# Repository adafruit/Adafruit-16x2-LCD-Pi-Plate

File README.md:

# PCB files for Adafruit 16x2 LCD Pi Plate for Raspberry Pi

<a href="http://www.adafruit.com/products/1110"><br/>Click here to purchase one from the Adafruit shop</a>

* https://www.adafruit.com/product/1110
* https://www.adafruit.com/product/1115
* http://www.adafruit.com/products/1109

This new Adafruit Pi Plate makes it easy to use a blue and white 16x2 Character LCD. [We really like the 16x2 Character LCDs we stock in the shop](http://www.adafruit.com/products/181). Unfortunately, these LCDs do require quite a few digital pins, 6 to control the LCD and then another 1 to control the backlight for a total of 7 pins. That's nearly all the GPIO available on a Pi!

With this in mind, we wanted to make it easier for people to get these LCD into their projects so we devised a Pi plate that lets you control __a 16x2 Character LCD, up to 3 backlight pins AND 5 keypad pins using only the two I2C pins on the R-Pi!__ The best part is you don't really lose those two pins either, since you can stick i2c-based sensors, RTCs, etc and have them share the I2C bus. This is a super slick way to add a display without all the wiring hassle.

__New, we've updated this Pi plate so the buttons on on the right side, which makes it a little more mechanically stable__

This pi plate is perfect for when you want to build a stand-alone project with its own user interface. The 4 directional buttons plus select button allows basic control without having to attach a bulky computer.

The plate is designed for both Revision 1 and Revision 2 Raspberry Pi's. It uses the I2C (SDA/SCL) pins. We have a special xtra-tall 26-pin header so the plate sits above the USB and Ethernet jacks. __For Pi Model B+ and Pi 2,__ the resistors sit right above the new set of USB ports. To keep them from shorting against the metal, a piece of electrical tape must be placed onto the USB ports.

__This product comes as a kit!__ Included is a high quality PCB and all the components (buttons, header etc). __A 16x2 Character blue&white monochrome LCD is included!__ Assembly is easy, even if you've never soldered before and the kit can be completed in 30 minutes. [Check the product tutorial page for assembly instructions before purchasing](http://learn.adafruit.com/adafruit-16x2-character-lcd-plus-keypad-for-raspberry-pi). You may get a 2-row or 1-row connector LCD, either will work fine.

[We also have some handy Python code to help you easily talk to the LCD and buttons](http://learn.adafruit.com/adafruit-16x2-character-lcd-plus-keypad-for-raspberry-pi).
You can also easily query the 5 keypad buttons to get input through the library, so you get extra buttons without using any more pins. The buttons are automatically de-bounced inside the library.

At this time, the code and plate can control the white backlight on or off. There is no support for PWM control of the backlight at this time, so if you need to have more granular control of the backlight, this plate can't do that (the I2C expander does not have PWM output).

## License

Adafruit invests time and resources providing this open source design, 
please support Adafruit and open-source hardware by purchasing 
products from Adafruit!

Designed by Limor Fried/Ladyada for Adafruit Industries.
Released under Creative Commons - Attribution/Share-Alike
All text above must be included in any redistribution

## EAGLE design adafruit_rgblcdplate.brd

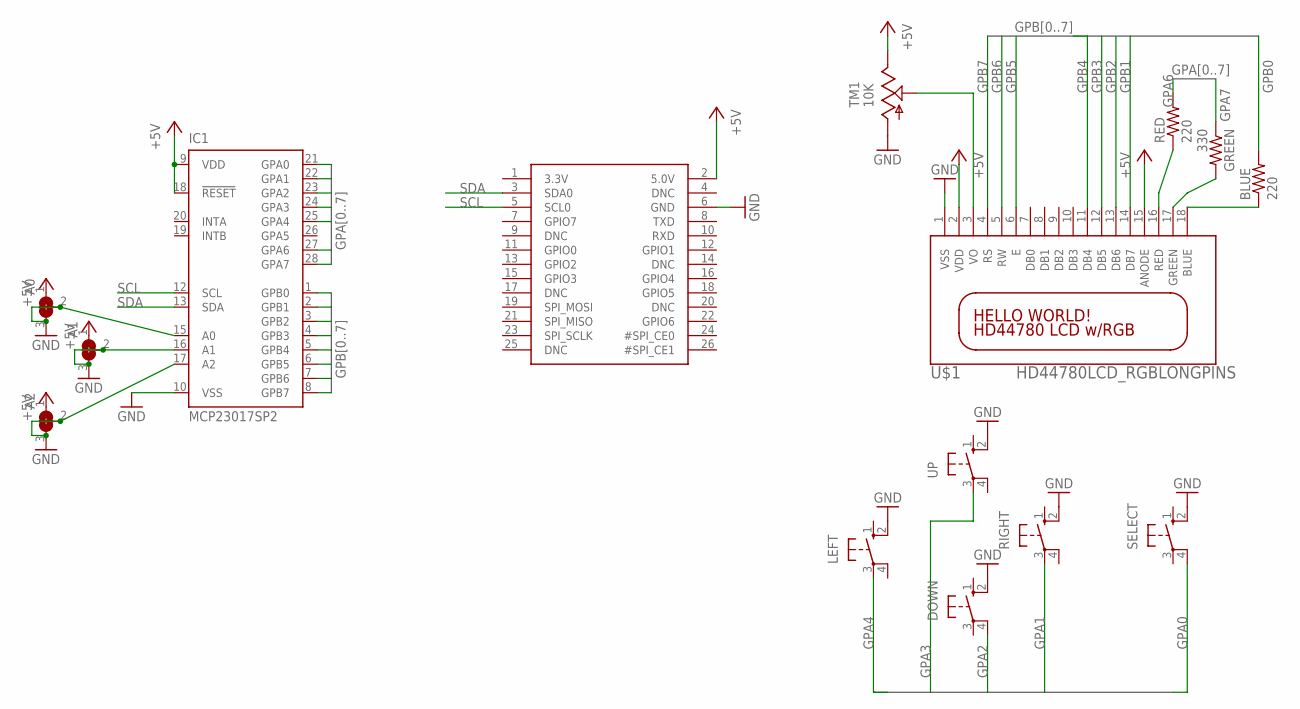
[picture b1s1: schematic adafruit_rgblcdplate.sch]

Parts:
A0, A1, A2: SOLDERJUMPER_2WAY; SOLDERJUMPER_2WAY_OPEN_NOPASTE
BLUE: 220; 0207/10
DOWN: 10-XX; B3F-10XX
GREEN: 330; 0207/10
IC1: MCP23017SP2; DIL28-3-ROUND
LEFT: 10-XX; B3F-10XX
RED: 220; 0207/10
RIGHT: 10-XX; B3F-10XX
SELECT: 10-XX; B3F-10XX
TM1: 10K; 6MM
U$1: HD44780LCD_RGBLONGPINS; LCD1602-RGB
U$4: RASPBERRYPI_BB; RASBERRYPI_SHIELD
UP: 10-XX; B3F-10XX

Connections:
+5V: A0.1, A1.1, A2.1, IC1.9 (VDD), IC1.18 (!RESET), TM1.E, U$1.2 (VDD), U$1.15 (ANODE), U$4.2 (5.0V)
GND: A0.2, A0.3, A1.2, A1.3, A2.2, A2.3, DOWN.2 (S1), IC1.10 (VSS), IC1.15 (A0), IC1.16 (A1), IC1.17 (A2), LEFT.2 (S1), RIGHT.2 (S1), SELECT.2 (S1), TM1.A, U$1.1 (VSS), U$4.6 (GND), UP.2 (S1)
GPA0: IC1.21 (GPA0), SELECT.4 (P1)
GPA1: IC1.22 (GPA1), RIGHT.3
GPA2: DOWN.4 (P1), IC1.23 (GPA2)
GPA3: IC1.24 (GPA3), UP.3
GPA4: IC1.25 (GPA4), LEFT.3
GPA6: IC1.27 (GPA6), RED.2
GPA7: GREEN.1, IC1.28 (GPA7)
GPB0: BLUE.2, IC1.1 (GPB0)
GPB1: IC1.2 (GPB1), U$1.14 (DB7)
GPB2: IC1.3 (GPB2), U$1.13 (DB6)
GPB3: IC1.4 (GPB3), U$1.12 (DB5)
GPB4: IC1.5 (GPB4), U$1.11 (DB4)
GPB5: IC1.6 (GPB5), U$1.6 (E)
GPB6: IC1.7 (GPB6), U$1.5 (RW)
GPB7: IC1.8 (GPB7), U$1.4 (RS)
unnamed: BLUE.1, U$1.18 (BLUE)
unnamed: GREEN.2, U$1.17 (GREEN)
unnamed: RED.1, U$1.16 (RED)
unnamed: TM1.S, U$1.3 (VO)
SCL: IC1.12 (SCL), U$4.5 (SCL0)
SDA: IC1.13 (SDA), U$4.3 (SDA0)

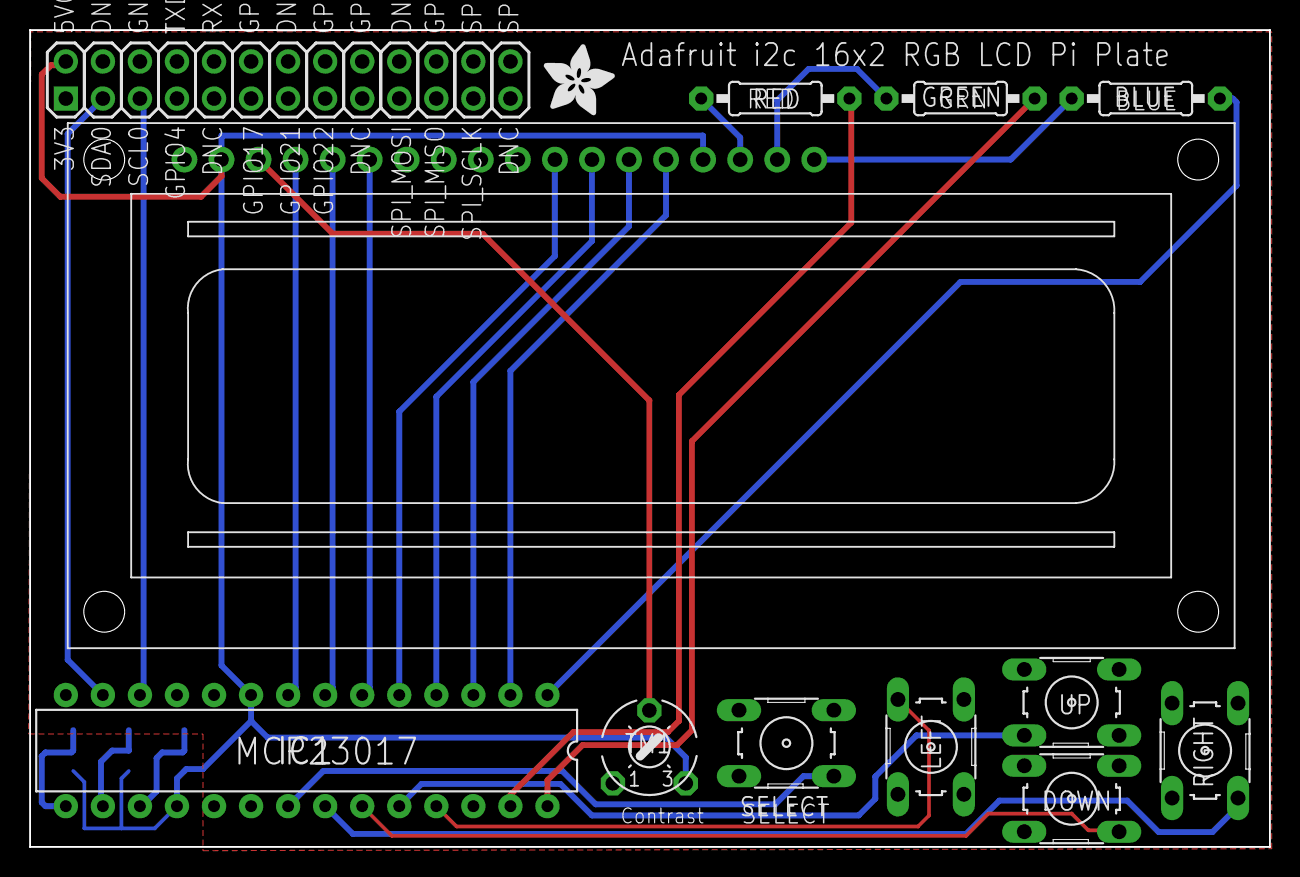
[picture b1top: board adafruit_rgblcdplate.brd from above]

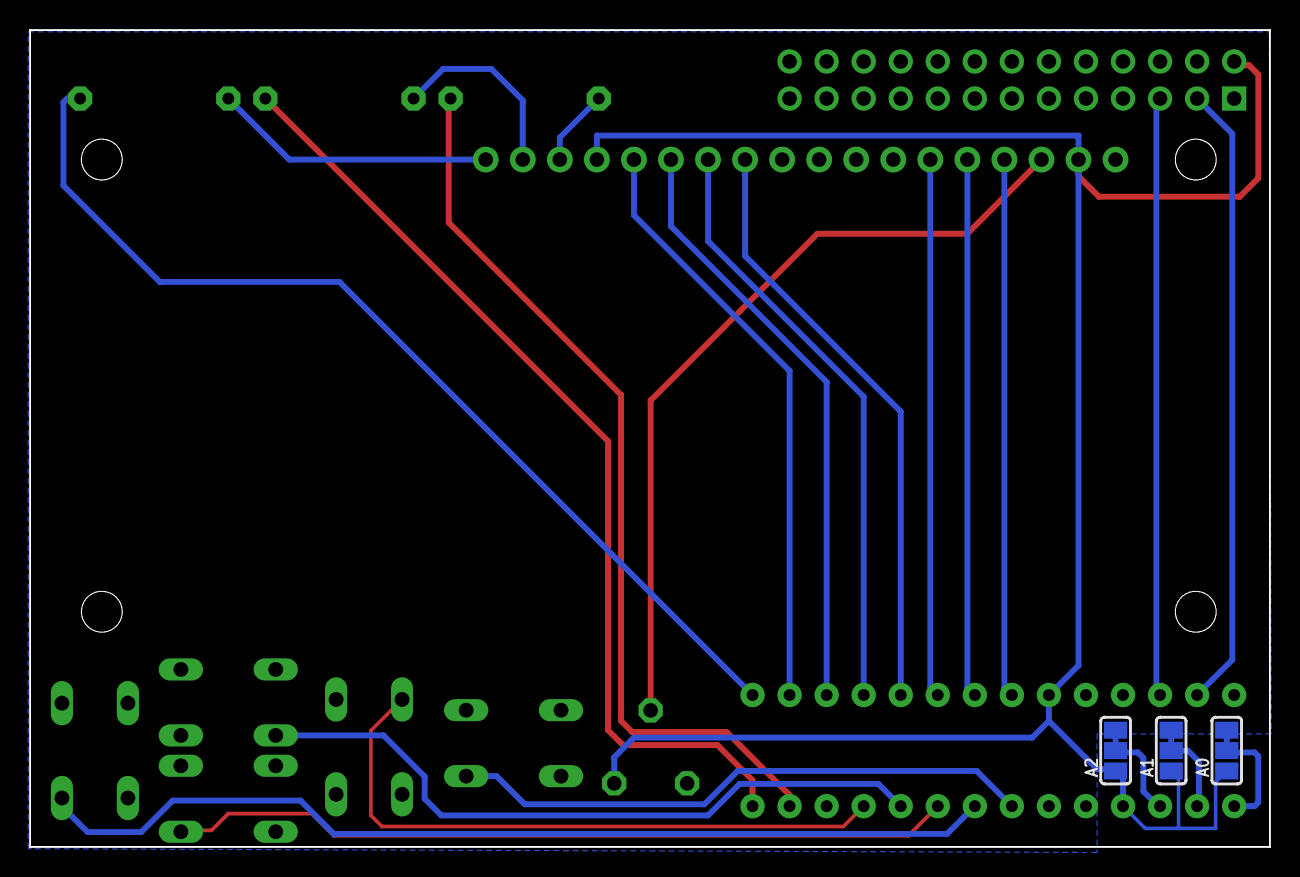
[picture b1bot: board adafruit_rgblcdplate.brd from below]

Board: 2 copper layers, 85.0 x 56.0 mm, 16 parts (3 on the bottom side), 23 nets.

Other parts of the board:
U$2: ADAFRUIT_5MM

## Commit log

2014-01-02 buttons-on-right version
2014-01-02 readme w/links
2019-05-08 readme + image
